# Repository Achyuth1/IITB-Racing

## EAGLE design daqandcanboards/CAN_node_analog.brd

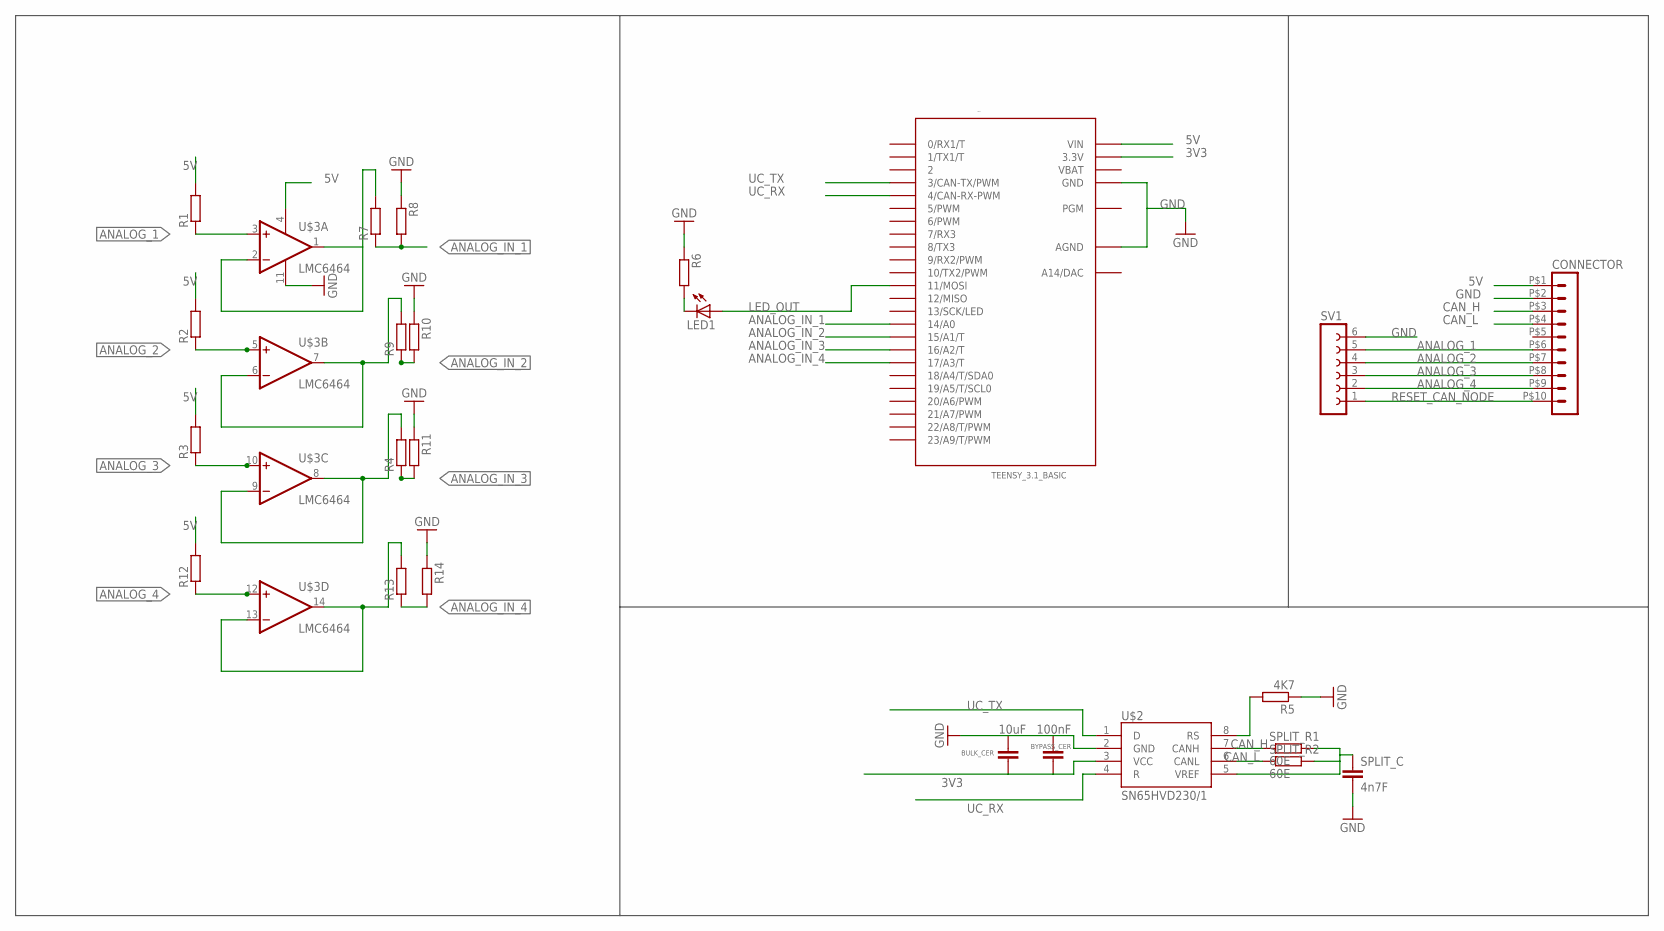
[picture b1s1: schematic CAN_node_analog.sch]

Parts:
BULK_CER: 10uF; C0805
BYPASS_CER: 100nF; C0805
CONNECTOR: HEADER_POS10_43045-1012; 43045-1012
LED1: LED1206; LED-1206
R1, R2, R3, R4, R6, R7, R8, R9, R10, R11, R12, R13, R14: R-EU_R0805; R0805
R5: 4K7; R0805
SPLIT_C: 4n7F; C0805
SPLIT_R1, SPLIT_R2: 60E; R0805
SV1: FE06-1; FE06
U$1: TEENSY_3.1_BASIC
U$2: SN65HVD230/1; SO8
U$3: LMC6464; SO14_LONGPADS

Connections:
3V3: BULK_CER.1, BYPASS_CER.1, U$1.3.3V, U$1.3.3V1 (3.3V), U$2.3 (VCC)
5V: CONNECTOR.P$1 (1), R1.2, R2.2, R3.2, R12.2, U$1.VIN, U$3.4 (V+)
.: R7.2, U$3.1 (OUT), U$3.2 (-IN)
.2: R9.2, U$3.6 (-IN), U$3.7 (OUT)
.3: R4.2, U$3.8 (OUT), U$3.9 (-IN)
.4: R13.2, U$3.13 (-IN), U$3.14 (OUT)
ANALOG_1: CONNECTOR.P$6 (6), R1.1, SV1.5, U$3.3 (+IN)
ANALOG_2: CONNECTOR.P$7 (7), R2.1, SV1.4, U$3.5 (+IN)
ANALOG_3: CONNECTOR.P$8 (8), R3.1, SV1.3, U$3.10 (+IN)
ANALOG_4: CONNECTOR.P$9 (9), R12.1, SV1.2, U$3.12 (+IN)
ANALOG_IN_1: R7.1, R8.2, U$1.14/A0
ANALOG_IN_2: R9.1, R10.2, U$1.15/A1 (15/A1/T)
ANALOG_IN_3: R4.1, R11.2, U$1.16/A2 (16/A2/T)
ANALOG_IN_4: R13.1, R14.2, U$1.17/A3 (17/A3/T)
CAN_H: CONNECTOR.P$3 (3), SPLIT_R1.1, U$2.7 (CANH)
CAN_L: CONNECTOR.P$4 (4), SPLIT_R2.1, U$2.6 (CANL)
GND: BULK_CER.2, BYPASS_CER.2, CONNECTOR.P$2 (2), R5.1, R6.1, R8.1, R10.1, R11.1, R14.1, SPLIT_C.2, SV1.6, U$1.AGND, U$1.GND, U$1.GND1 (GND), U$2.2 (GND), U$3.11 (V-)
LED_OUT: LED1.A, U$1.11 (11/MOSI)
unnamed: LED1.C, R6.2
unnamed: R5.2, U$2.8 (RS)
unnamed: SPLIT_C.1, SPLIT_R1.2, SPLIT_R2.2, U$2.5 (VREF)
RESET_CAN_NODE: CONNECTOR.P$10 (10), SV1.1
UC_RX: U$1.4 (4/CAN-RX-PWM), U$2.4 (R)
UC_TX: U$1.3 (3/CAN-TX/PWM), U$2.1 (D)
VBAT: U$1.VBAT

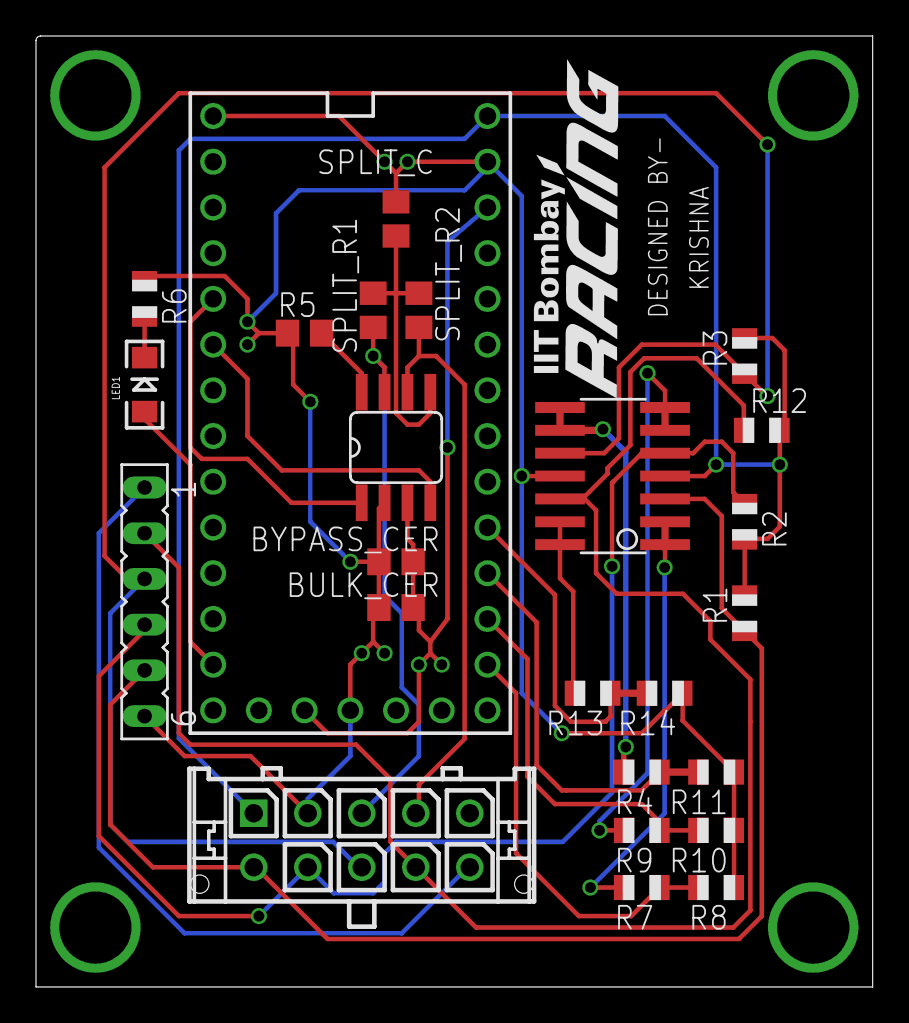
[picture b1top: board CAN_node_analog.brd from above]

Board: 2 copper layers, 46.5 x 52.8 mm, 26 parts (0 on the bottom side), 24 nets.

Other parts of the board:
U$4: IITBR_LOGO2

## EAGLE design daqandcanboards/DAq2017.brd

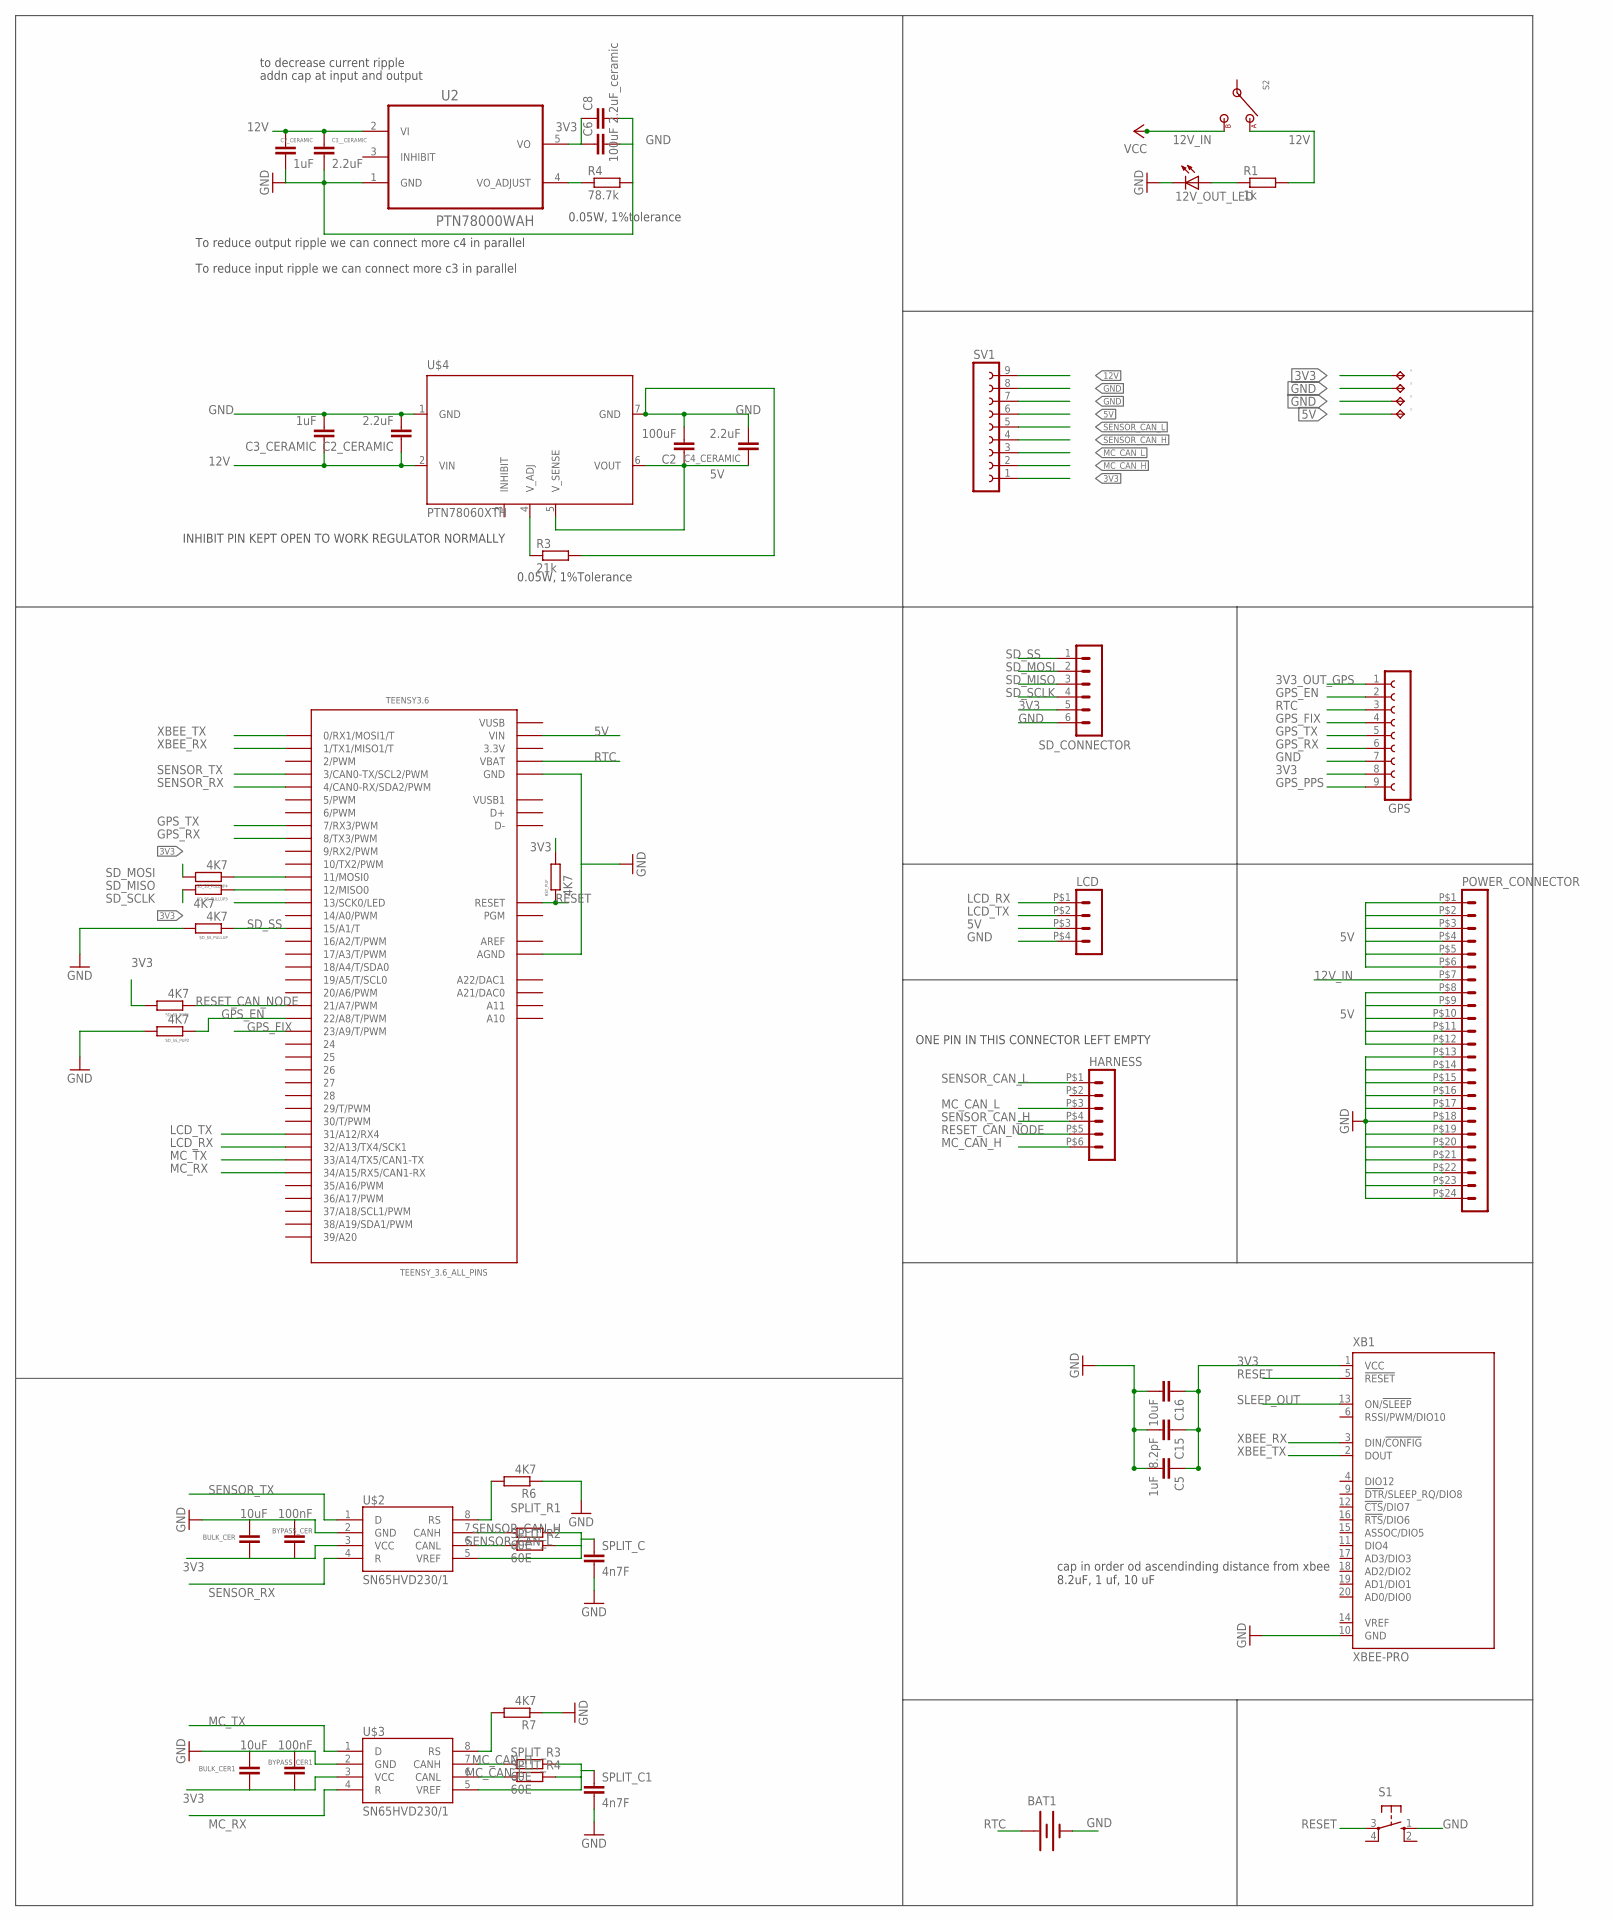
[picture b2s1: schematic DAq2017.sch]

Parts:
12V_OUT_LED: LEDCHIPLED_1206; CHIPLED_1206
BAT1: BATTERY20PTH; BATTCOM_20MM_PTH
BULK_CER, BULK_CER1: 10uF; C0805
BYPASS_CER, BYPASS_CER1: 100nF; C0805
C2, C6: 100uF; C0805
C2_CERAMIC, C3__CERAMIC, C4_CERAMIC: 2.2uF; C0805
C3_CERAMIC, C5, C7_CERAMIC: 1uF; C0805
C8: 2.2uF_ceramic; C0805
C15: 8.2pF; C0805
C16: 10uF; C0805
GPS: FE09-1; FE09
HARNESS: HEADER_POS6_43045-0612; 43045-0612
LCD: HEADER_POS4_43045-0412; 43045-0412
POWER_CONNECTOR: HEADER_POS24_43045-2412; 43045-2412
R1: 1k; R0805
R3: 21k; R0805
R4: 78.7k; R0805
R6, R7: 4K7; R0805
RST_PUP: 4K7; R0805
S1: 10-XX; B3F-10XX
S2: STS121PC04
SD_SS_PULLUP, SD_SS_PULLUP3, SD_SS_PULLUP4: 4K7; R0805
SD_SS_PUP1, SD_SS_PUP2: 4K7; R0805
SPLIT_C, SPLIT_C1: 4n7F; C0805
SPLIT_R1, SPLIT_R2, SPLIT_R3, SPLIT_R4: 60E; R0805
SV1: FE09-1; FE09
TEENSY3.6: TEENSY_3.6_ALL_PINS
TP2, TP3, TP4, TP5: TPPAD1-17Y; P1-17Y
U2: PTN78000WAH; TI_PTN78000WAH
U$2, U$3: SN65HVD230/1; SO8
U$4: PTN78060XTH; PTN78060X_TH
X4: SD_CONNECTOR; MA06-1
XB1: XBEE-PRO

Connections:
3.3V: TEENSY3.6.3.3V, TEENSY3.6.3.3V3 (3.3V), TEENSY3.6.3.3V4 (3.3V)
3V3: BULK_CER.1, BULK_CER1.1, BYPASS_CER.1, BYPASS_CER1.1, C5.1, C6.1, C8.1, C15.1, C16.1, GPS.8, RST_PUP.2, SD_SS_PULLUP3.2, SD_SS_PULLUP4.2, SD_SS_PUP1.2, SV1.1, TP2.TP, U2.5 (VO), U$2.3 (VCC), U$3.3 (VCC), X4.5, XB1.1 (VCC)
3V3_OUT_GPS: GPS.1
5V: C2.1, C4_CERAMIC.1, LCD.P$3 (3), POWER_CONNECTOR.P$1 (1), POWER_CONNECTOR.P$2 (2), POWER_CONNECTOR.P$3 (3), POWER_CONNECTOR.P$4 (4), POWER_CONNECTOR.P$5 (5), POWER_CONNECTOR.P$6 (6), POWER_CONNECTOR.P$8 (8), POWER_CONNECTOR.P$9 (9), POWER_CONNECTOR.P$10 (10), POWER_CONNECTOR.P$11 (11), POWER_CONNECTOR.P$12 (12), SV1.6, TEENSY3.6.VIN, TP5.TP, U$4.5 (V_SENSE), U$4.6 (VOUT)
12V: C2_CERAMIC.1, C3_CERAMIC.1, C3__CERAMIC.1, C7_CERAMIC.1, R1.2, S2.1, SV1.9, U2.2 (VI), U$4.2 (VIN)
12V_IN: POWER_CONNECTOR.P$7 (7), S2.3
AREF: TEENSY3.6.AREF
GND: 12V_OUT_LED.C, BAT1.2 (-), BULK_CER.2, BULK_CER1.2, BYPASS_CER.2, BYPASS_CER1.2, C2.2, C2_CERAMIC.2, C3_CERAMIC.2, C3__CERAMIC.2, C4_CERAMIC.2, C5.2, C6.2, C7_CERAMIC.2, C8.2, C15.2, C16.2, GPS.7, LCD.P$4 (4), POWER_CONNECTOR.P$13 (13), POWER_CONNECTOR.P$14 (14), POWER_CONNECTOR.P$15 (15), POWER_CONNECTOR.P$16 (16), POWER_CONNECTOR.P$17 (17), POWER_CONNECTOR.P$18 (18), POWER_CONNECTOR.P$19 (19), POWER_CONNECTOR.P$20 (20), POWER_CONNECTOR.P$21 (21), POWER_CONNECTOR.P$22 (22), POWER_CONNECTOR.P$23 (23), POWER_CONNECTOR.P$24 (24), R3.2, R4.2, R6.1, R7.1, S1.1 (S), SD_SS_PULLUP.2, SD_SS_PUP2.2, SPLIT_C.2, SPLIT_C1.2, SV1.7, SV1.8, TEENSY3.6.AGND, TEENSY3.6.GND, TEENSY3.6.GND1 (GND), TEENSY3.6.GND3 (GND), TEENSY3.6.GND4 (GND), TEENSY3.6.GND6 (GND), TP3.TP, TP4.TP, U2.1 (GND), U$2.2 (GND), U$3.2 (GND), U$4.1 (GND), U$4.7 (GND), X4.6, XB1.10 (GND)
GPS_EN: GPS.2, SD_SS_PUP2.1, TEENSY3.6.22/A8 (22/A8/T/PWM)
GPS_FIX: GPS.4, TEENSY3.6.23/A9 (23/A9/T/PWM)
GPS_PPS: GPS.9
GPS_RX: GPS.6, TEENSY3.6.8 (8/TX3/PWM)
GPS_TX: GPS.5, TEENSY3.6.7 (7/RX3/PWM)
LCD_RX: LCD.P$1 (1), TEENSY3.6.32/A13 (32/A13/TX4/SCK1)
LCD_TX: LCD.P$2 (2), TEENSY3.6.31/A12 (31/A12/RX4)
LULZ: R6.2, U$2.8 (RS)
MC_CAN_H: HARNESS.P$6 (6), SPLIT_R3.1, SV1.2, U$3.7 (CANH)
MC_CAN_L: HARNESS.P$3 (3), SPLIT_R4.1, SV1.3, U$3.6 (CANL)
MC_RX: TEENSY3.6.34/A15 (34/A15/RX5/CAN1-RX), U$3.4 (R)
MC_TX: TEENSY3.6.33/A14 (33/A14/TX5/CAN1-TX), U$3.1 (D)
unnamed: R3.1, U$4.4 (V_ADJ)
unnamed: R4.1, U2.4 (VO_ADJUST)
unnamed: 12V_OUT_LED.A, R1.1
unnamed: R7.2, U$3.8 (RS)
unnamed: SPLIT_C1.1, SPLIT_R3.2, SPLIT_R4.2, U$3.5 (VREF)
unnamed: SPLIT_C.1, SPLIT_R1.2, SPLIT_R2.2, U$2.5 (VREF)
RESET: RST_PUP.1, S1.3, TEENSY3.6.RESET, XB1.5 (!RESET)
RESET_CAN_NODE: HARNESS.P$5 (5), SD_SS_PUP1.1, TEENSY3.6.21/A7 (21/A7/PWM)
RTC: BAT1.1 (+), GPS.3, TEENSY3.6.VBAT
SD_MISO: SD_SS_PULLUP3.1, TEENSY3.6.12 (12/MISO0), X4.3
SD_MOSI: SD_SS_PULLUP4.1, TEENSY3.6.11 (11/MOSI0), X4.2
SD_SCLK: TEENSY3.6.13 (13/SCK0/LED), X4.4
SD_SS: SD_SS_PULLUP.1, TEENSY3.6.15/A1 (15/A1/T), X4.1
SENSOR_CAN_H: HARNESS.P$4 (4), SPLIT_R1.1, SV1.4, U$2.7 (CANH)
SENSOR_CAN_L: HARNESS.P$1 (1), SPLIT_R2.1, SV1.5, U$2.6 (CANL)
SENSOR_RX: TEENSY3.6.4 (4/CAN0-RX/SDA2/PWM), U$2.4 (R)
SENSOR_TX: TEENSY3.6.3 (3/CAN0-TX/SCL2/PWM), U$2.1 (D)
SLEEP_OUT: XB1.13 (ON/!SLEEP)
VUSB: TEENSY3.6.VUSB
VUSB1: TEENSY3.6.VUSB1
XBEE_RX: TEENSY3.6.1 (1/TX1/MISO1/T), XB1.3 (DIN/!CONFIG)
XBEE_TX: TEENSY3.6.0 (0/RX1/MOSI1/T), XB1.2 (DOUT)

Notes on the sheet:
0.05W, 1%Tolerance
INHIBIT PIN KEPT OPEN TO WORK REGULATOR NORMALLY
To reduce output ripple we can connect more c4 in parallel
To reduce input ripple we can connect more c3 in parallel
0.05W, 1%tolerance
to decrease current ripple
addn cap at input and output
ONE PIN IN THIS CONNECTOR LEFT EMPTY
cap in order od ascendinding distance from xbee 8.2uF, 1 uf, 10 uF

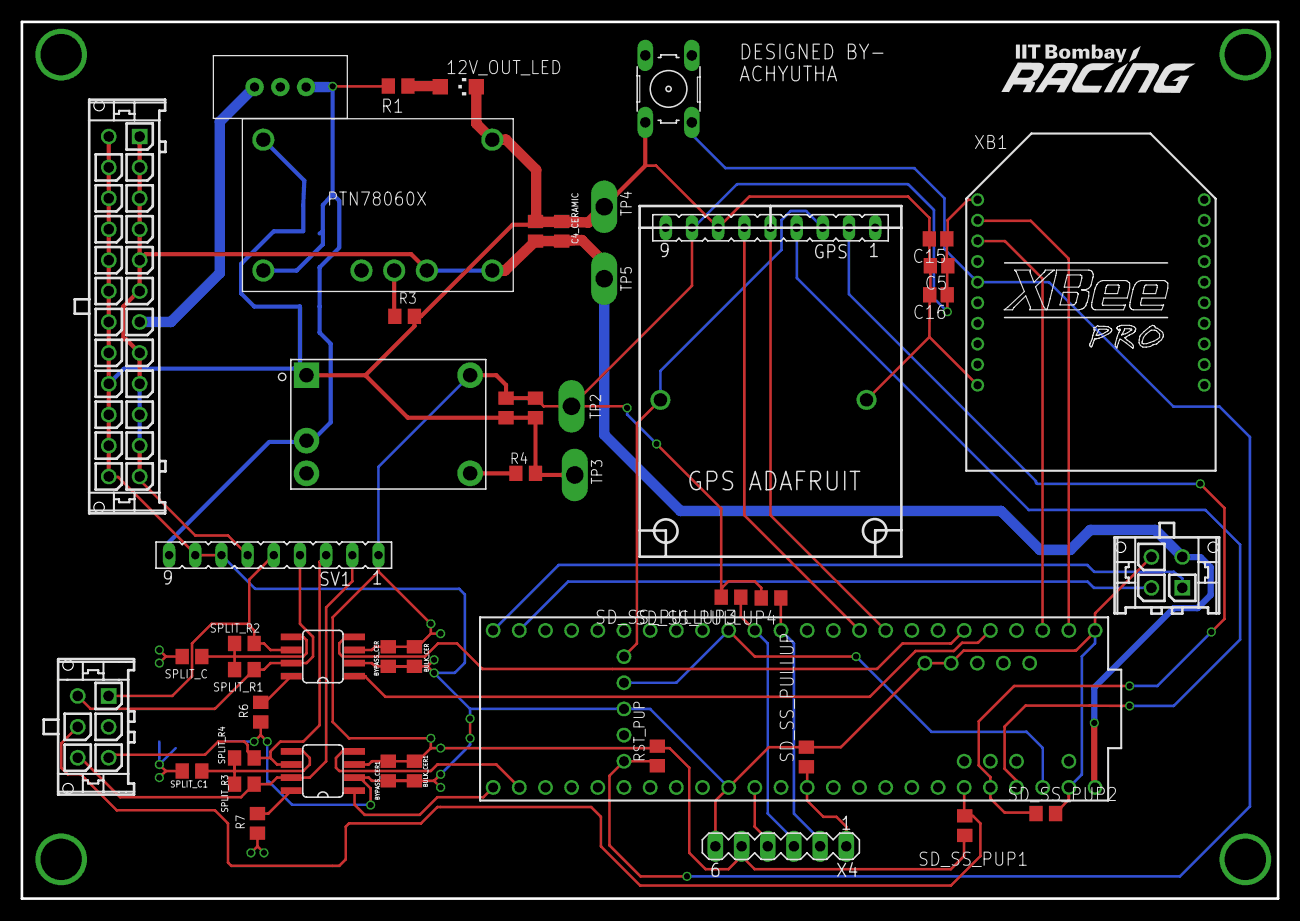
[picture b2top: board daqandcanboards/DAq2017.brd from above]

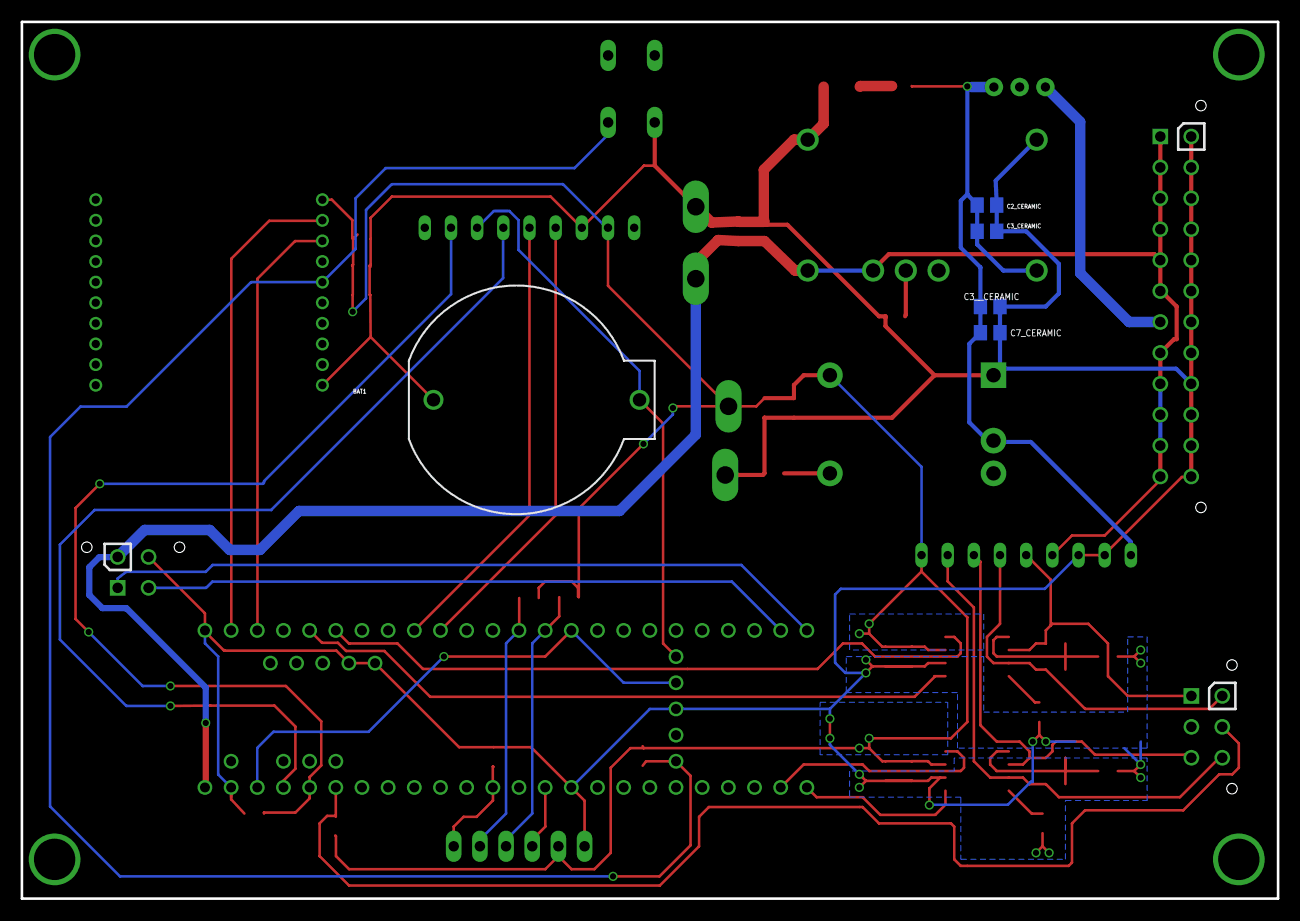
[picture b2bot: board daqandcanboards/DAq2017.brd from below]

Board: 2 copper layers, 121.9 x 85.1 mm, 53 parts (5 on the bottom side), 36 nets.

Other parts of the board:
U$5: IITBR_LOGO2

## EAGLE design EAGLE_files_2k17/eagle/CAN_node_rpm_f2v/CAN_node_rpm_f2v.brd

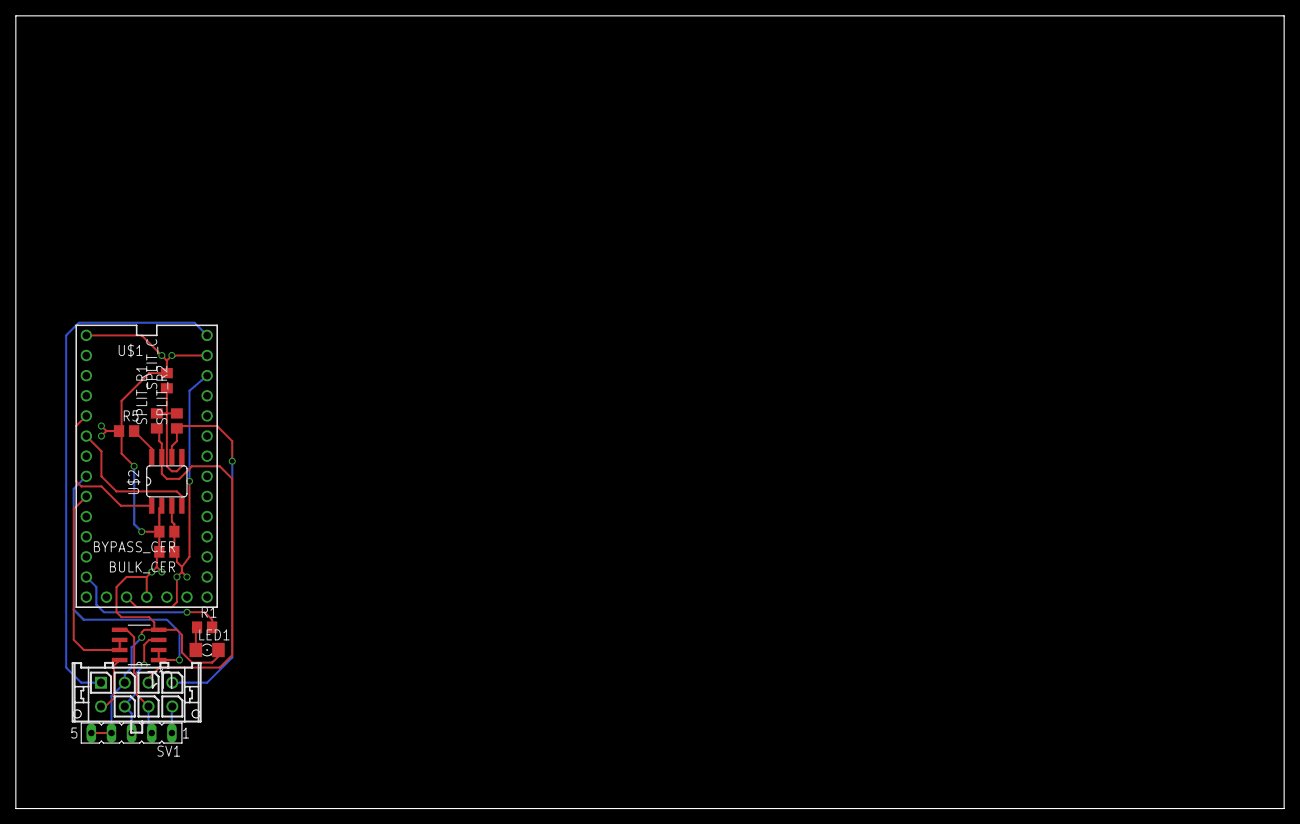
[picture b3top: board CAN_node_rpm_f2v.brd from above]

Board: 2 copper layers, 160.0 x 100.0 mm, 13 parts (0 on the bottom side), 17 nets.

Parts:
BULK_CER: 10uF; C0805
BYPASS_CER: 100nF; C0805
LED1: LED_1206
R1: R0805
R5: 4K7; R0805
SPLIT_C: 4n7F; C0805
SPLIT_R1, SPLIT_R2: 60E; R0805
SV1: FE05-1
U1: TL082ID; SOIC127P600X175-8N
U$1: TEENSY_3.1_BASIC
U$2: SN65HVD230/1; SO8
X1: 43045-0812

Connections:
3V3: BULK_CER.1, BYPASS_CER.1, U$1.3.3V, U$1.3.3V1, U$2.3
5V: U$1.VIN, X1.P$1
12V: U1.8, X1.P$5
CAN_H: SPLIT_R1.1, U$2.7, X1.P$3
CAN_L: SPLIT_R2.1, U$2.6, X1.P$4
GND: BULK_CER.2, BYPASS_CER.2, LED1.C, R5.1, SPLIT_C.2, SV1.4, SV1.5, U1.4, U$1.AGND, U$1.GND, U$1.GND1, U$2.2, X1.P$2
LED_OUT: R1.2, U$1.11
unnamed: LED1.A, R1.1
unnamed: R5.2, U$2.8
unnamed: SPLIT_C.1, SPLIT_R1.2, SPLIT_R2.2, U$2.5
RESET_CAN_NODE: SV1.1, X1.P$8
RPM_1: SV1.3, U1.3, X1.P$6
RPM_2: SV1.2, U1.5, X1.P$7
RPM_IN_1: U1.1, U1.2, U$1.6
RPM_IN_2: U1.6, U1.7, U$1.7
UC_RX: U$1.4, U$2.4
UC_TX: U$1.3, U$2.1

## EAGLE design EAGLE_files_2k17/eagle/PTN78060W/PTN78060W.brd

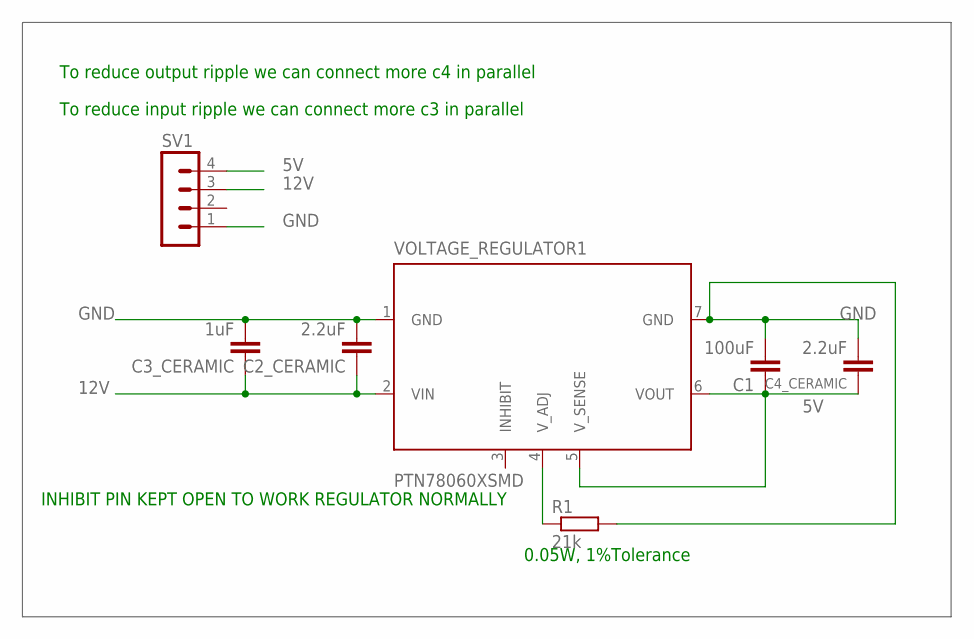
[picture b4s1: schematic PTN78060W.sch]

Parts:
C1: 100uF; C0805
C2_CERAMIC, C4_CERAMIC: 2.2uF; C0805
C3_CERAMIC: 1uF; C0805
R1: 21k; R0805
SV1: MA04-1
VOLTAGE_REGULATOR1: PTN78060XSMD; PTN78060X_SMD

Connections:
5V: C1.1, C4_CERAMIC.1, SV1.4, VOLTAGE_REGULATOR1.5 (V_SENSE), VOLTAGE_REGULATOR1.6 (VOUT)
12V: C2_CERAMIC.1, C3_CERAMIC.1, SV1.3, VOLTAGE_REGULATOR1.2 (VIN)
GND: C1.2, C2_CERAMIC.2, C3_CERAMIC.2, C4_CERAMIC.2, R1.2, SV1.1, VOLTAGE_REGULATOR1.1 (GND), VOLTAGE_REGULATOR1.7 (GND)
unnamed: R1.1, VOLTAGE_REGULATOR1.4 (V_ADJ)

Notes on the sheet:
0.05W, 1%Tolerance
INHIBIT PIN KEPT OPEN TO WORK REGULATOR NORMALLY
To reduce output ripple we can connect more c4 in parallel
To reduce input ripple we can connect more c3 in parallel

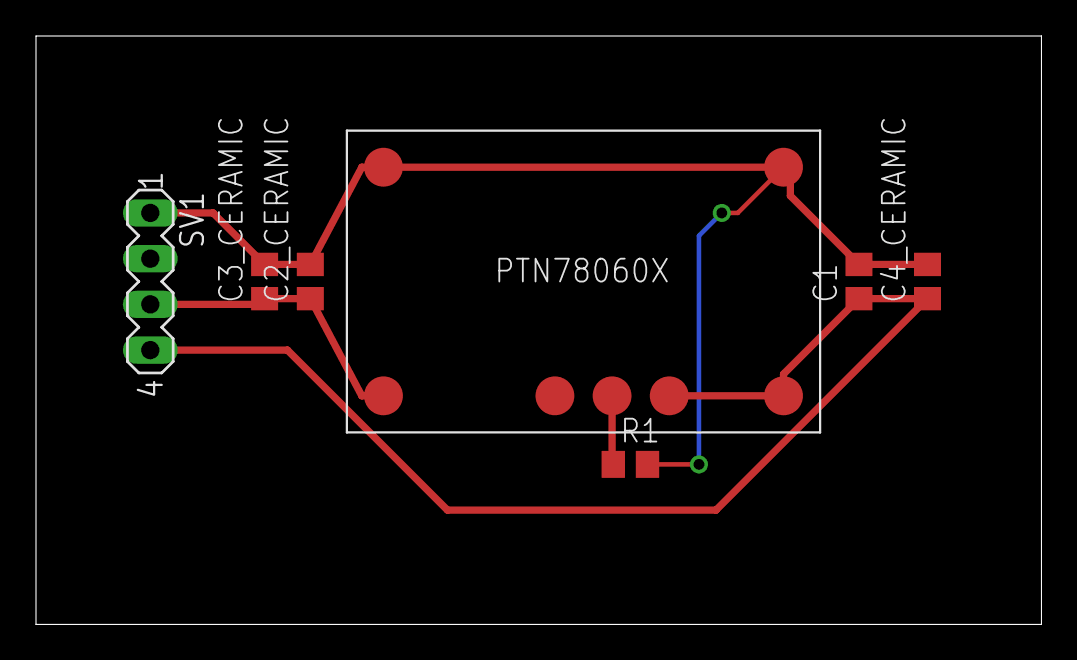
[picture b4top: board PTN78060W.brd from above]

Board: 2 copper layers, 55.9 x 32.7 mm, 7 parts (0 on the bottom side), 4 nets.

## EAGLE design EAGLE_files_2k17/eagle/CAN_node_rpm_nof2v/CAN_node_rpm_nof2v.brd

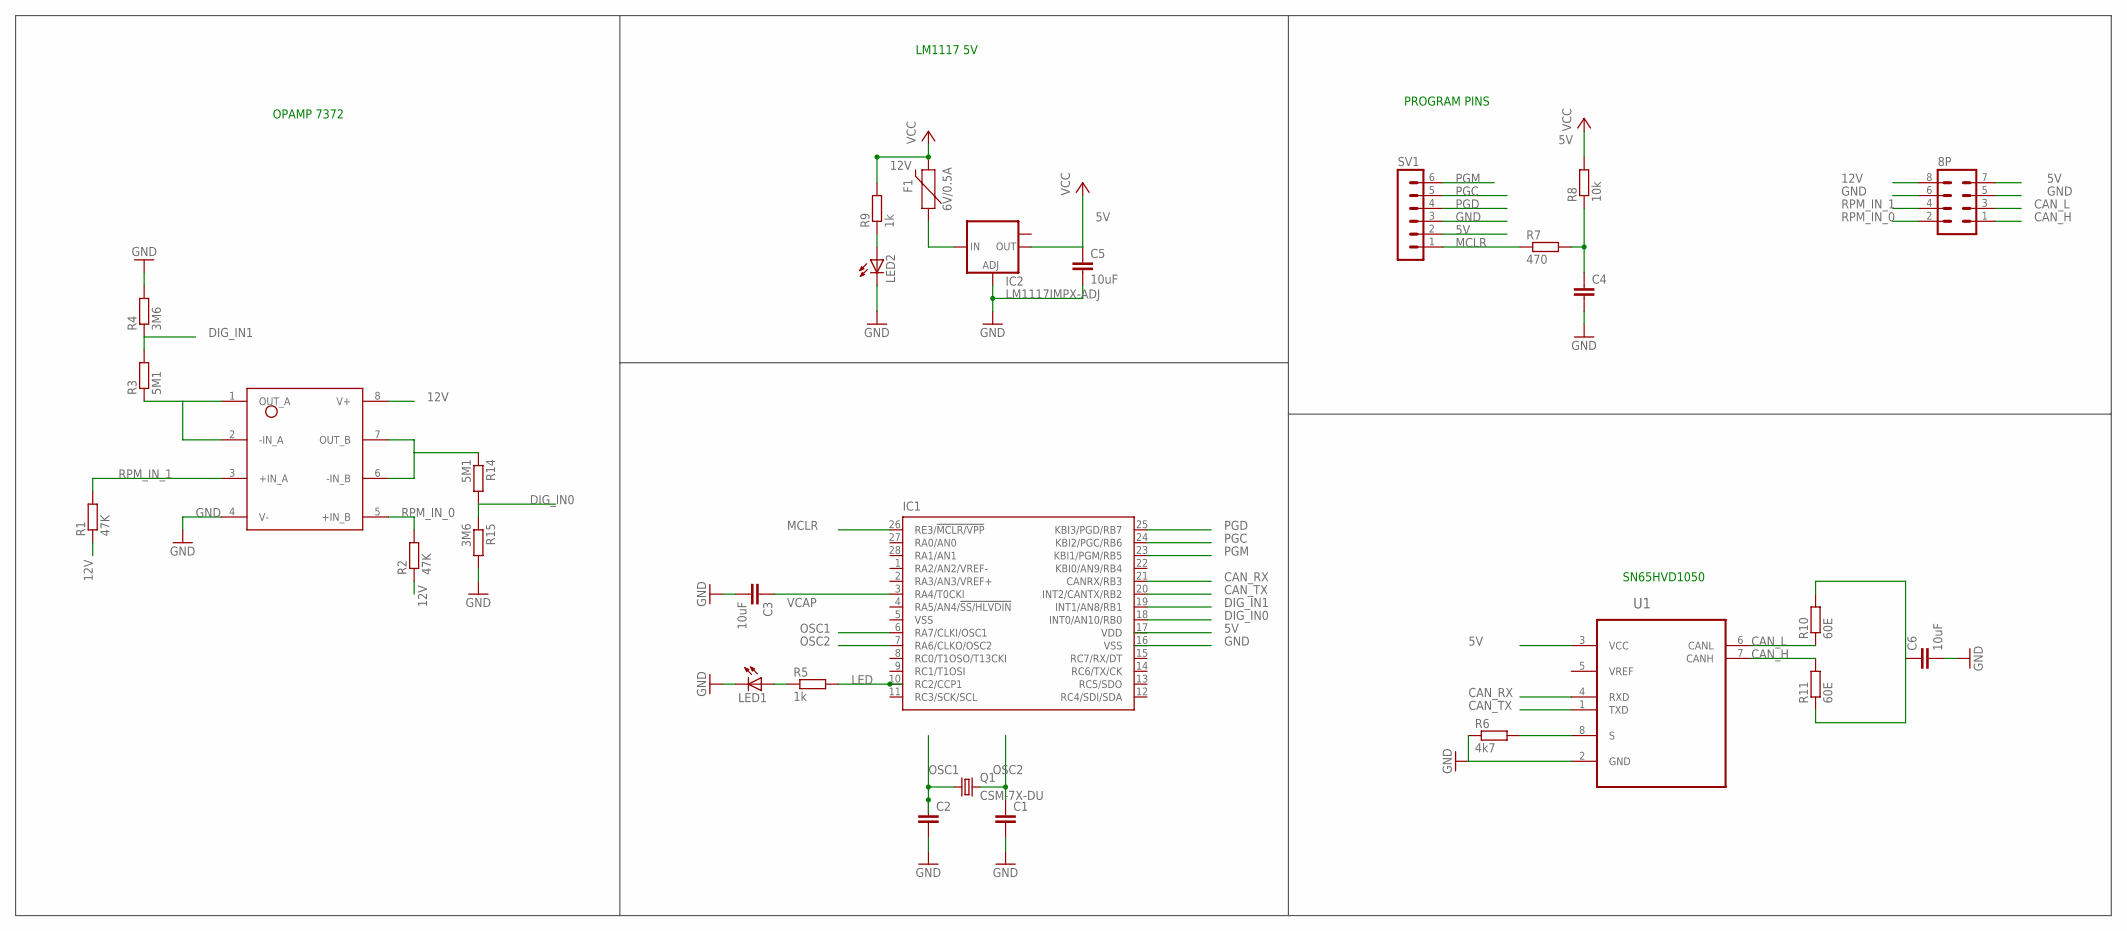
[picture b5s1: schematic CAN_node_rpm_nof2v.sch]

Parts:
8P: MA04-2
C1, C2, C4: C-EUC0805; C0805
C3, C5, C6: 10uF; C0805
F1: 6V/0.5A; 1206
IC1: MICROCHIP_PIC18F2580-I/ML; MICROCHIP_QFN28-ML_6X6MM
IC2: LM1117IMPX-ADJ; SOT223
LED1, LED2: LED_LEDCHIPLED_1206; LED_CHIPLED_1206
LM1: 7372
Q1: CSM-7X-DU
R1, R2: 47K; R0805
R3, R14: 5M1; R0805
R4, R15: 3M6; R0805
R5, R9: 1k; R0805
R6: 4k7; R0805
R7: 470; R0805
R8: 10k; R0805
R10, R11: 60E; R0805
SV1: MA06-1
U1: TEXAS-INSTRUMENTS_BY_ELEMENT14_BATCH_1_SN65HVD105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; TEXAS-INSTRUMENTS_BY_ELEMENT14_BATCH_1_SOIC127P600X175-8N

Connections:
5V: 8P.7, C5.1, IC1.17 (VDD), IC2.2 (OUT), R8.2, SV1.2, U1.3 (VCC)
12V: 8P.8, F1.2, LM1.8 (V+), R1.1, R2.1, R9.2
CAN_H: 8P.1, R11.2, U1.7 (CANH)
CAN_L: 8P.3, R10.1, U1.6 (CANL)
CAN_RX: IC1.21 (CANRX/RB3), U1.4 (RXD)
CAN_TX: IC1.20 (INT2/CANTX/RB2), U1.1 (TXD)
DIG_IN0: IC1.18 (INT0/AN10/RB0), R14.2, R15.1
DIG_IN1: IC1.19 (INT1/AN8/RB1), R3.2, R4.1
GND: 8P.5, 8P.6, C1.2, C2.2, C3.2, C4.2, C5.2, C6.2, IC1.16 (VSS), IC2.1 (ADJ), LED1.C, LED2.C, LM1.4 (V-), R4.2, R6.1, R15.2, SV1.3, U1.2 (GND)
LED: IC1.10 (RC2/CCP1), R5.2
MCLR: IC1.26 (RE3/!MCLR/VPP), R7.1, SV1.1
unnamed: LED1.A, R5.1
unnamed: R6.2, U1.8 (S)
unnamed: C4.1, R7.2, R8.1
unnamed: F1.1, IC2.3 (IN)
unnamed: LED2.A, R9.1
unnamed: C6.1, R10.2, R11.1
unnamed: LM1.1 (OUT_A), LM1.2 (-IN_A), R3.1
unnamed: LM1.6 (-IN_B), LM1.7 (OUT_B), R14.1
OSC1: C2.1, IC1.6 (RA7/CLKI/OSC1), Q1.1
OSC2: C1.1, IC1.7 (RA6/CLKO/OSC2), Q1.2
PGC: IC1.24 (KBI2/PGC/RB6), SV1.5
PGD: IC1.25 (KBI3/PGD/RB7), SV1.4
PGM: IC1.23 (KBI1/PGM/RB5), SV1.6
RPM_IN_0: 8P.2, LM1.5 (+IN_B), R2.2
RPM_IN_1: 8P.4, LM1.3 (+IN_A), R1.2
VCAP: C3.1, IC1.3 (RA4/T0CKI)
VSS: IC1.5 (VSS)

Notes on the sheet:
PROGRAM PINS
SN65HVD1050
OPAMP 7372
LM1117 5V

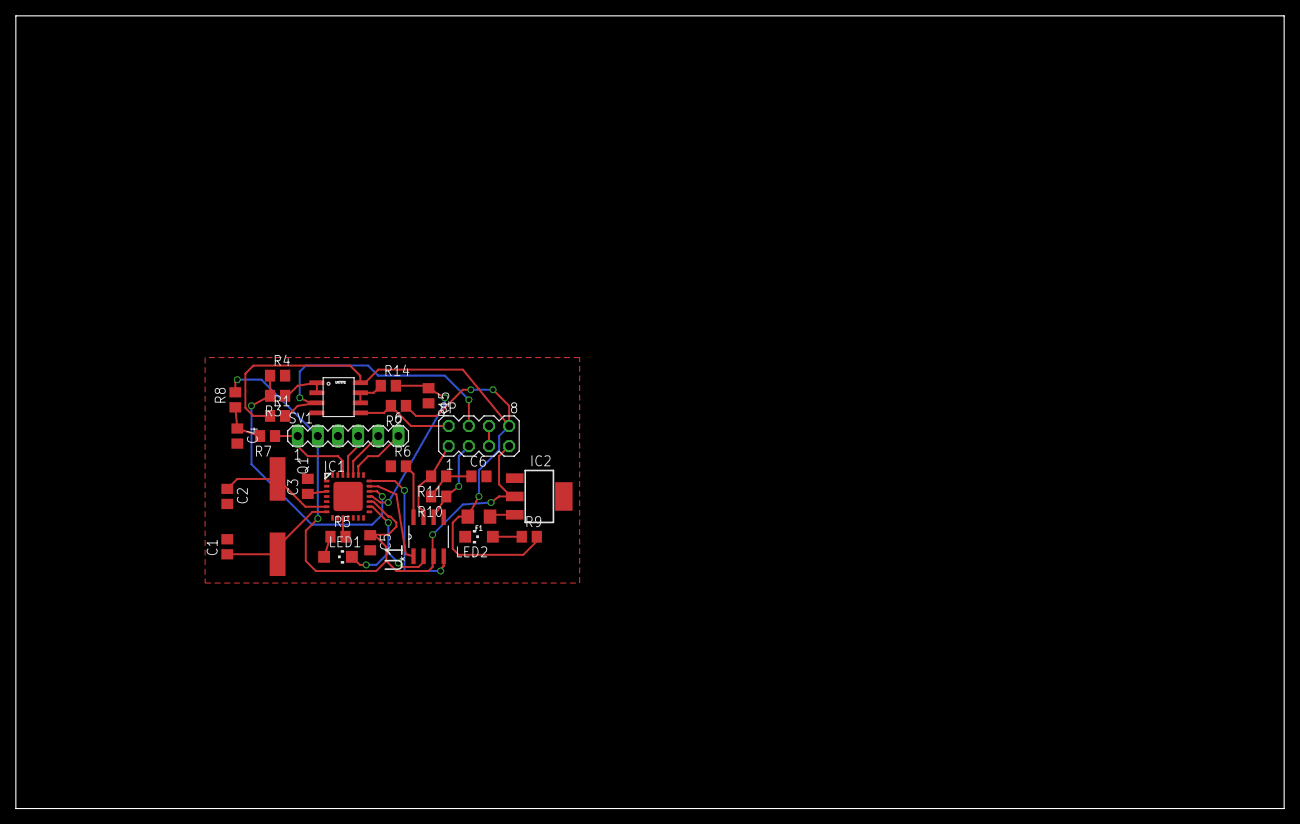
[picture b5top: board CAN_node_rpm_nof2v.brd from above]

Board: 2 copper layers, 160.0 x 100.0 mm, 29 parts (0 on the bottom side), 27 nets.

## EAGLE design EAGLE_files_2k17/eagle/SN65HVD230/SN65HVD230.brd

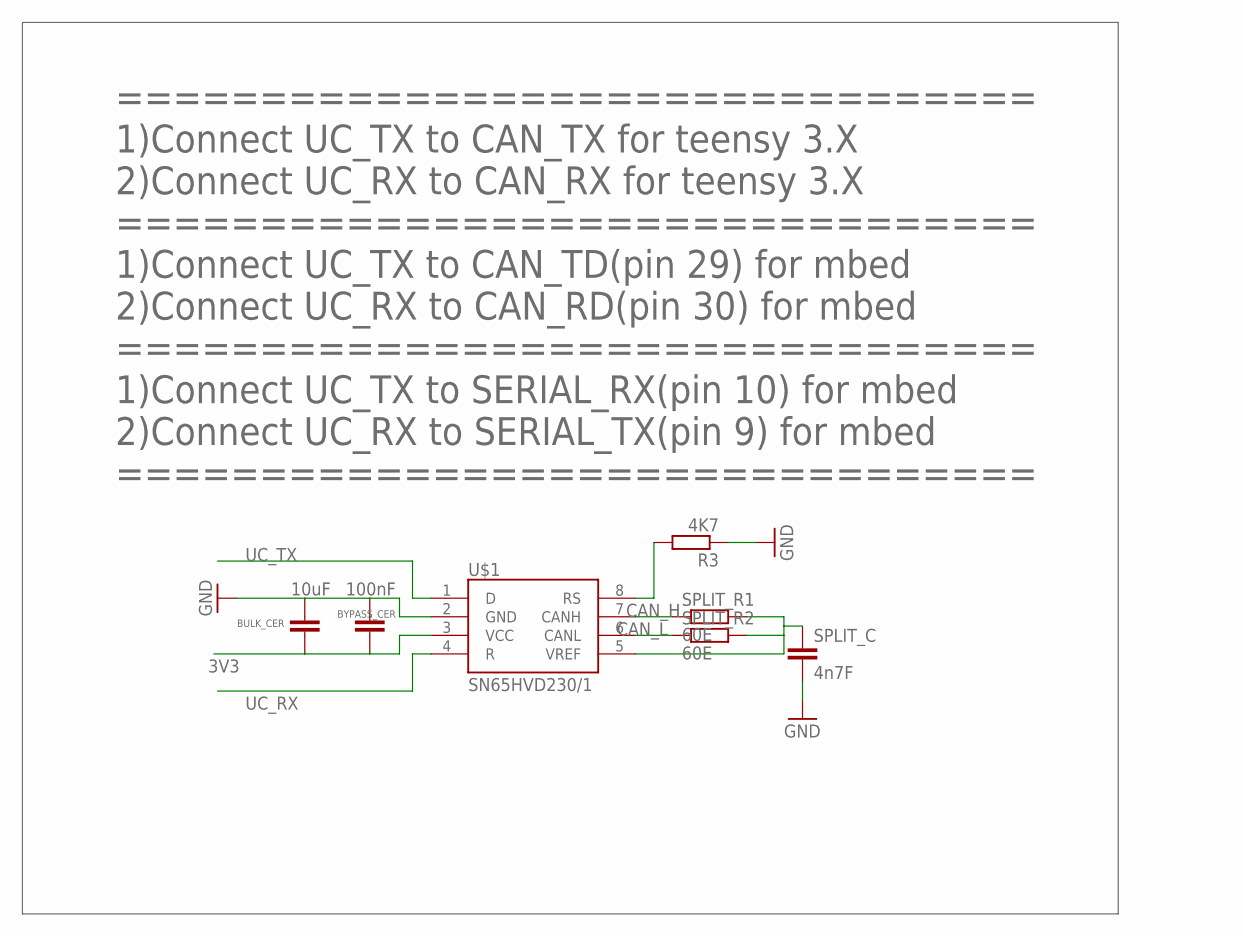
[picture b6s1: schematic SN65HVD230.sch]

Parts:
BULK_CER: 10uF; C0805
BYPASS_CER: 100nF; C0805
R3: 4K7; R0805
SPLIT_C: 4n7F; C0805
SPLIT_R1, SPLIT_R2: 60E; R0805
U$1: SN65HVD230/1; SO8

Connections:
3V3: BULK_CER.1, BYPASS_CER.1, U$1.3 (VCC)
CAN_H: SPLIT_R1.1, U$1.7 (CANH)
CAN_L: SPLIT_R2.1, U$1.6 (CANL)
GND: BULK_CER.2, BYPASS_CER.2, R3.1, SPLIT_C.2, U$1.2 (GND)
unnamed: R3.2, U$1.8 (RS)
unnamed: SPLIT_C.1, SPLIT_R1.2, SPLIT_R2.2, U$1.5 (VREF)
UC_RX: U$1.4 (R)
UC_TX: U$1.1 (D)

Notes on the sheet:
================================ 1)Connect UC_TX to CAN_TX for teensy 3.X 2)Connect UC_RX to CAN_RX for teensy 3.X ================================ 1)Connect UC_TX to CAN_TD(pin 29) for mbed 2)Connect UC_RX to CAN_RD(pin 30) for mbed ================================ 1)Connect UC_TX to SERIAL_RX(pin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

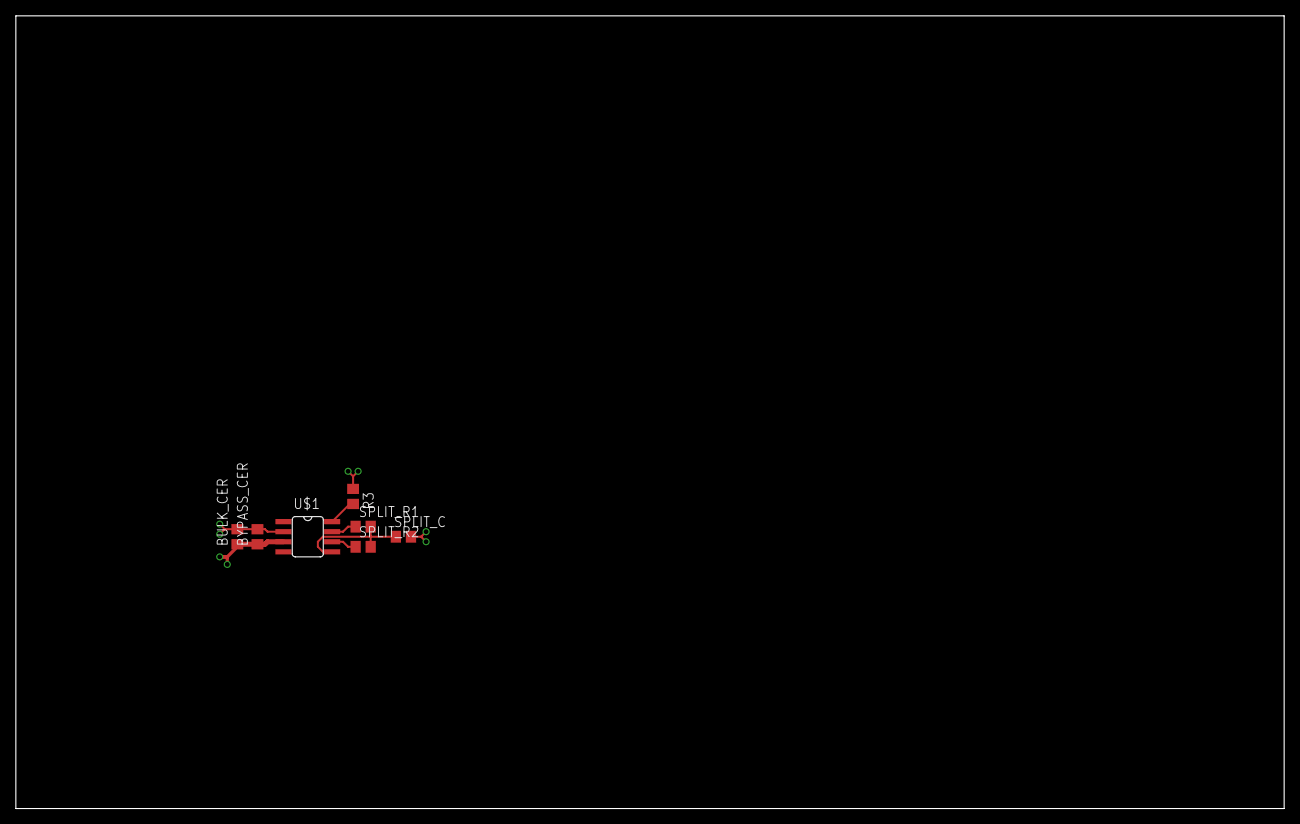
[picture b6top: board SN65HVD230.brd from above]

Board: 2 copper layers, 160.0 x 100.0 mm, 7 parts (0 on the bottom side), 6 nets.

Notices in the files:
parts and their libraries:
sparkfun_fuses: Licensing: Creative Commons ShareAlike 4.0 International - https://creativecommons.org/licenses/by-sa/4.0
SparkFun-Electromechanical: Licensing: CC v3.0 Share-Alike You are welcome to use this library for commercial purposes.
